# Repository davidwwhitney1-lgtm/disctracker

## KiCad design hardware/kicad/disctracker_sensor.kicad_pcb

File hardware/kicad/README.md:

# DiscTracker sensor board — KiCad 9 project

Open `disctracker_sensor.kicad_pro` in KiCad 9.
- Schematic `disctracker_sensor.kicad_sch`: ERC 0 errors / 0 warnings.
- PCB `disctracker_sensor.kicad_pcb`: **DRC 0 violations, 0 unconnected, schematic parity clean** (all severities).
- Ready-to-order files in `fab/` (see "Ordering").

## Board
| | |
|---|---|
| Size | 56 mm round, flat at x = +26.5 mm for the USB-C plug |
| Stack | 4 layers, 0.8 mm: F.Cu signals + GND pour · In1 **solid GND plane (no signals)** · In2 +3V3 pour (4 short signal segments) · B.Cu signals + GND pour |
| Rules | 0.127 mm tracks (0.25 mm power), 0.12 mm clearance, vias 0.45/0.25 mm — within JLCPCB 4-layer standard |
| Sensor face (top, machine assembled) | U1–U6, C1–C11, R1–R9, JP1 |
| XIAO face (bottom, hand-soldered) | M1 XIAO, BZ1 buzzer, C12, J1/J2 battery pads, TP1–TP4 trim pads, battery outline |
| Not fitted (pair B) | U4, U5, C7–C10, R7, R8 |

Coordinates (origin = U1 = board center, +X toward the USB-C flat, seen from the sensor face):
U2/U3 at (±20.00, 0), U4/U5 at (0, ±20.00), U6 at (0, −25.0), XIAO center (+15, 0) with USB-C at the flat,
battery center (−6.54, 0), holes at r = 25.6 mm (30°/150°/250°), trim pads at r = 22 mm on the diagonals.

## Assembly notes
1. JLCPCB assembles the sensor face (`fab/bom_jlc.csv`, `fab/cpl_jlc.csv`). The LSM6DSV320X has no LCSC number:
   have JLC source it, or consign 3 chips. Check part rotations in JLC's placement preview (pin-1 dots).
2. Bridge **JP1 pads 2–3** (buzzer) with solder.
3. Solder the XIAO flat on the bottom by its castellated edges. Its underside **VBAT and GND pads are plated holes**
   on this board: from the sensor face, feed solder into the two holes next to the XIAO outline to join them.
4. Solder BZ1 and C12 on the bottom; battery leads to J1 (+) / J2 (−); bond the battery inside its silkscreen outline.
5. Weigh and spin-balance the finished pod; add solder to TP1–TP4 to trim.

## Ordering (JLCPCB)
- PCB: upload `fab/disctracker_sensor_gerbers.zip` — 4 layers, 0.8 mm, any color, "specify layer sequence" not needed.
- Assembly: top side, `fab/bom_jlc.csv` + `fab/cpl_jlc.csv`. Passives use JLC basic parts (confirm stock).
- Full parts list incl. hand-soldered parts: `fab/bom_all.csv`. Board-only STEP for the housing CAD: `fab/disctracker_sensor.step`
  (export again from your own KiCad with 3D libraries installed to include the parts).

## Known items
- Two vias sit under **U5** (not fitted on the first build). Move them before fitting pair B; U1–U4 have nothing under them.
- MMC5603NJ footprint (`Package_BGA:WLP-4_0.86x0.86mm_P0.4mm`): confirm ball pitch/pad size against MEMSIC's drawing.
- LGA-14 footprint vs ST TN0018 land pattern: KiCad's standard pattern for this package family.
- XIAO underside SWD/NFC pads are present as unconnected copper (footprint from Seeed's OPL library, CC BY-SA 4.0).

## How it was built (`gen/`)
1. `gen.py` — schematic + symbol library (don't re-run once you edit in KiCad; it also rewrites the .kicad_pro).
2. `xiao_fp.py` — XIAO footprint tweaks (plated VBAT/GND holes, outline on fab layer).
3. `pcb.py <dir> <netlist>` — placement, outline, planes, keepouts, silkscreen, locked GND fan-out under each IMU.
4. `route.py` — Freerouting 2.1 autoroute (In1 kept as a plane), then GND pours.
5. `stitch.py` — GND stitching vias (3 mm grid); `fixups.py` + `padvia.py` — hand fixes for this route; `check_gnd.py` — GND connectivity check.
6. `fab.sh` + `jlc.py` — DRC, Gerbers, drills, pick-and-place, BOMs, STEP, renders.
Autorouting isn't deterministic, so `fixups.py` only applies to the committed route. From here on, edit the PCB in KiCad.

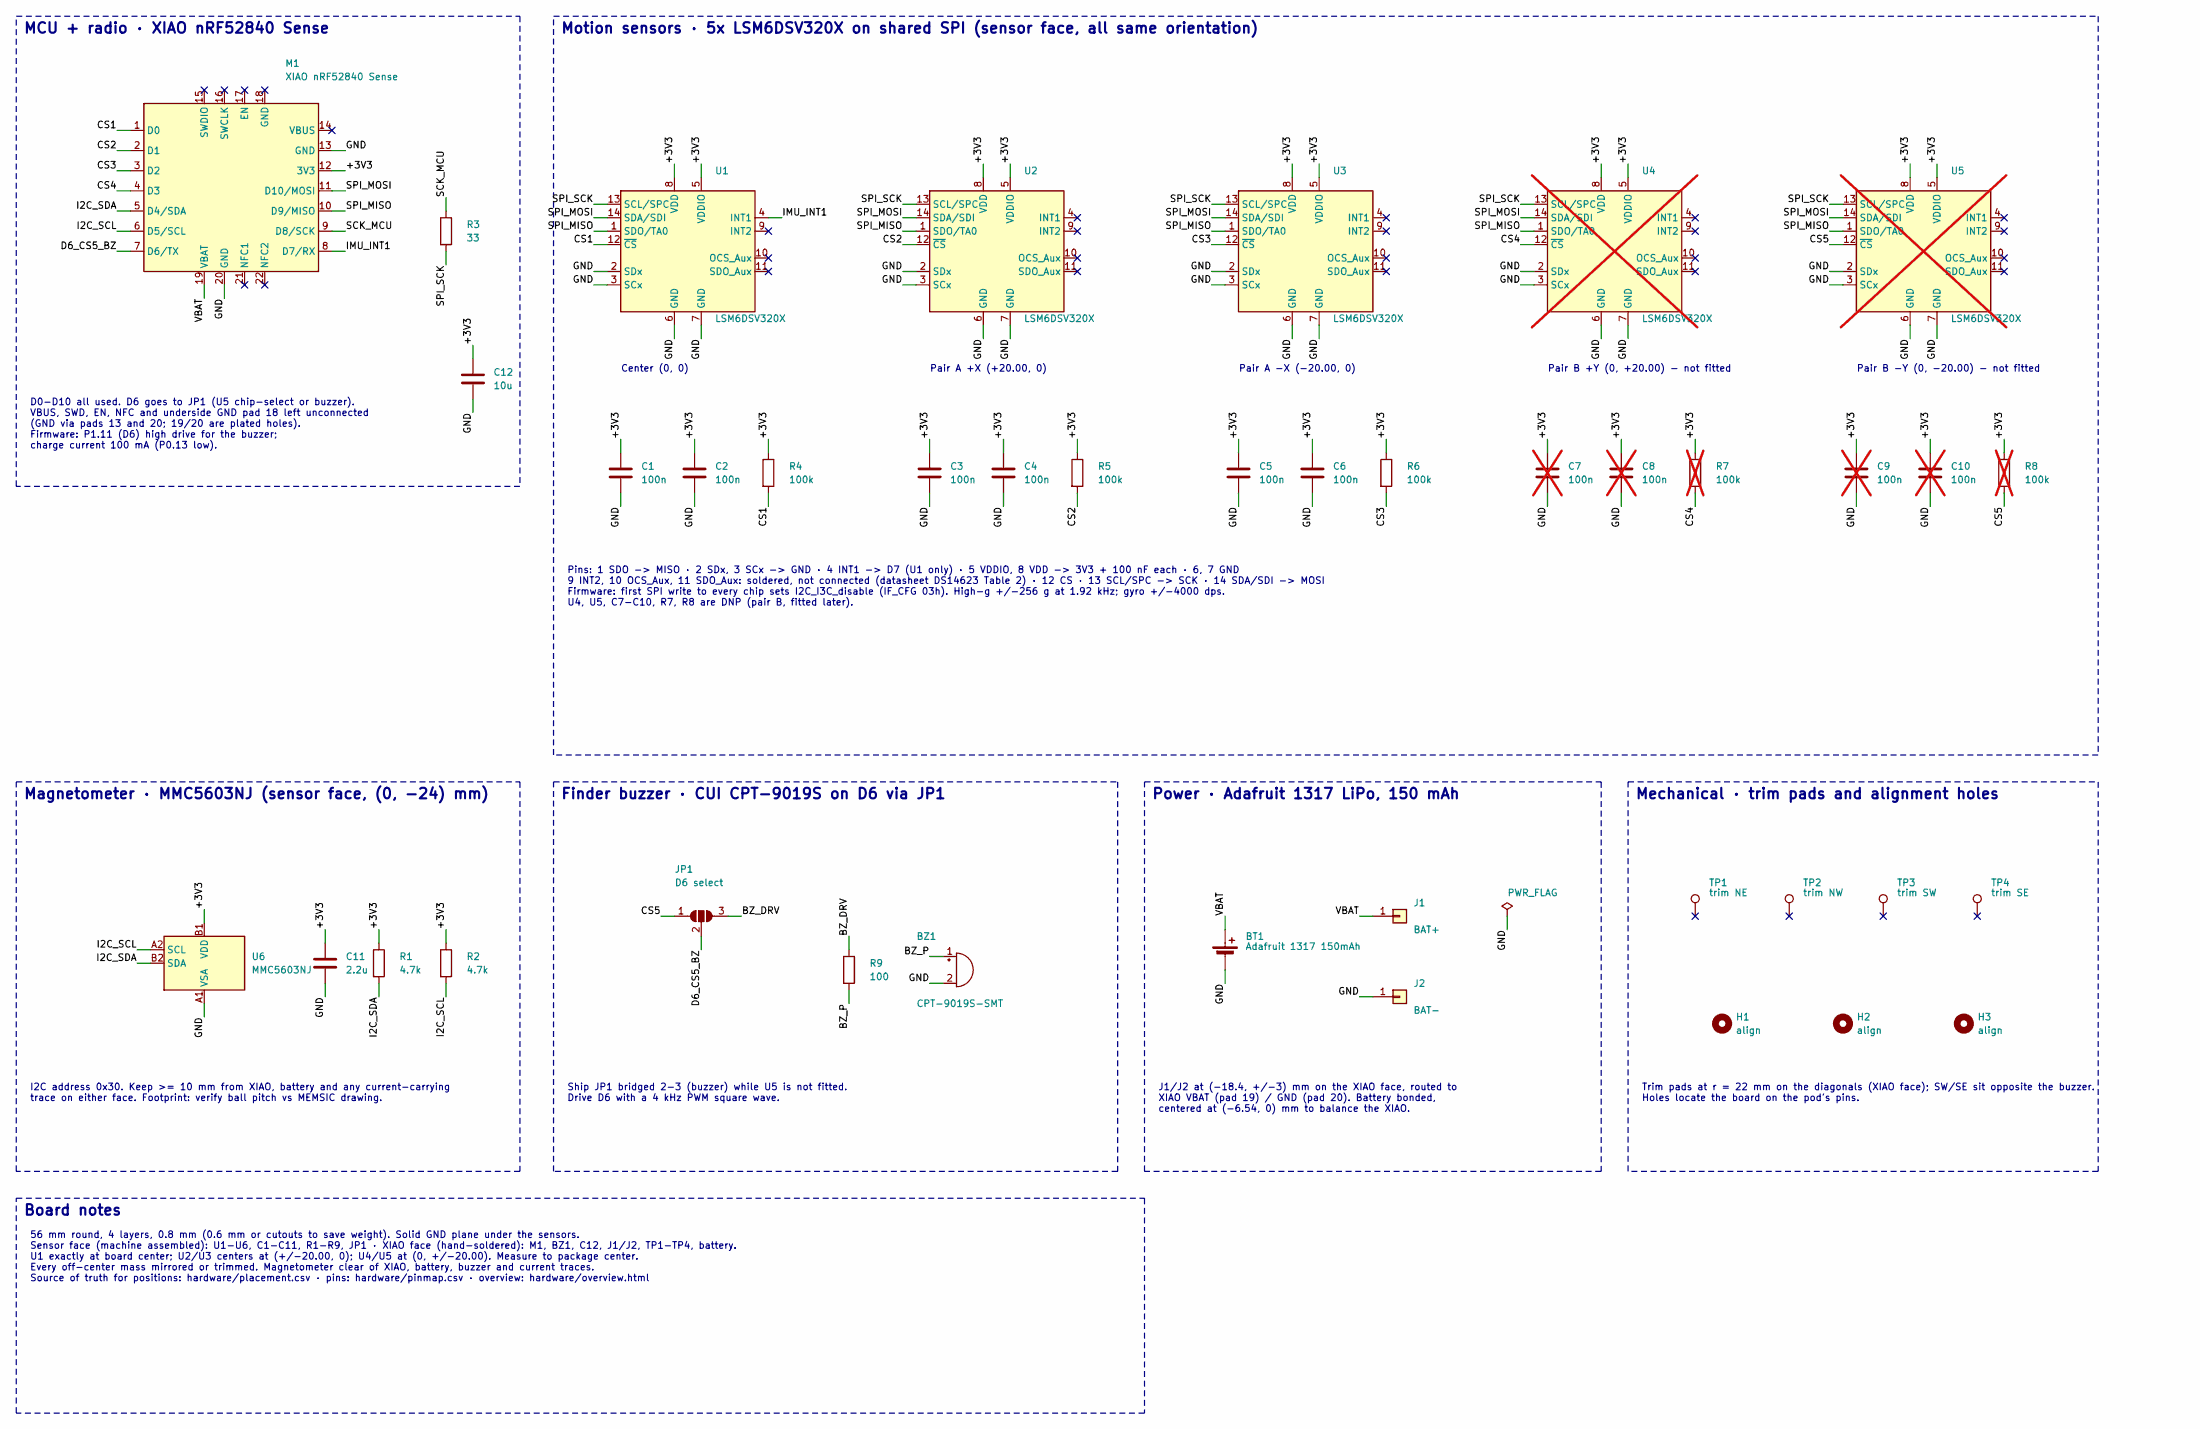
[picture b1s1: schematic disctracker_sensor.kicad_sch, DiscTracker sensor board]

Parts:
BT1: Adafruit 1317 150mAh; MPN Adafruit 1317
BZ1: CPT-9019S-SMT; Buzzer_CUI_CPT-9019S-SMT; MPN CPT-9019S-SMT-TR; LCSC C95163
C1, C2, C3, C4, C5, C6: 100n; C_0402_1005Metric
C7, C8, C9, C10: 100n; C_0402_1005Metric; not fitted
C11: 2.2u; C_0402_1005Metric
C12: 10u; C_0603_1608Metric
H1, H2, H3: align; MountingHole_2.1mm
J1: BAT+; SolderWirePad_1x01_SMD_1.5x3mm
J2: BAT-; SolderWirePad_1x01_SMD_1.5x3mm
JP1: D6 select; SolderJumper-3_P1.3mm_Open_RoundedPad1.0x1.5mm
M1: XIAO nRF52840 Sense; XIAO-nRF52840-SMD; MPN Seeed 102010469
R1, R2: 4.7k; R_0402_1005Metric
R3: 33; R_0402_1005Metric
R4, R5, R6: 100k; R_0402_1005Metric
R7, R8: 100k; R_0402_1005Metric; not fitted
R9: 100; R_0402_1005Metric
TP1: trim NE; TestPoint_Pad_3.0x3.0mm
TP2: trim NW; TestPoint_Pad_3.0x3.0mm
TP3: trim SW; TestPoint_Pad_3.0x3.0mm
TP4: trim SE; TestPoint_Pad_3.0x3.0mm
U1, U2, U3: LSM6DSV320X; LGA-14_3x2.5mm_P0.5mm_LayoutBorder3x4y; MPN LSM6DSV320XTR
U4, U5: LSM6DSV320X; LGA-14_3x2.5mm_P0.5mm_LayoutBorder3x4y; MPN LSM6DSV320XTR; not fitted
U6: MMC5603NJ; WLP-4_0.86x0.86mm_P0.4mm; MPN MMC5603NJ; LCSC C404328

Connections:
/+3V3: C1.1, C2.1, C3.1, C4.1, C5.1, C6.1, C7.1, C8.1, C9.1, C10.1, C11.1, C12.1, M1.12 (3V3), R1.1, R2.1, R4.1, R5.1, R6.1, R7.1, R8.1, U1.5 (VDDIO), U1.8 (VDD), U2.5 (VDDIO), U2.8 (VDD), U3.5 (VDDIO), U3.8 (VDD), U4.5 (VDDIO), U4.8 (VDD), U5.5 (VDDIO), U5.8 (VDD), U6.B1 (VDD)
/BZ_DRV: JP1.3 (B), R9.1
/BZ_P: BZ1.1 (+), R9.2
/CS1: M1.1 (D0), R4.2, U1.12 (~CS)
/CS2: M1.2 (D1), R5.2, U2.12 (~CS)
/CS3: M1.3 (D2), R6.2, U3.12 (~CS)
/CS4: M1.4 (D3), R7.2, U4.12 (~CS)
/CS5: JP1.1 (A), R8.2, U5.12 (~CS)
/D6_CS5_BZ: JP1.2 (C), M1.7 (D6/TX)
/GND: BT1.2 (-), BZ1.2 (-), C1.2, C2.2, C3.2, C4.2, C5.2, C6.2, C7.2, C8.2, C9.2, C10.2, C11.2, C12.2, J2.1, M1.13 (GND), M1.20 (GND), U1.2 (SDx), U1.3 (SCx), U1.6 (GND), U1.7 (GND), U2.2 (SDx), U2.3 (SCx), U2.6 (GND), U2.7 (GND), U3.2 (SDx), U3.3 (SCx), U3.6 (GND), U3.7 (GND), U4.2 (SDx), U4.3 (SCx), U4.6 (GND), U4.7 (GND), U5.2 (SDx), U5.3 (SCx), U5.6 (GND), U5.7 (GND), U6.A1 (VSA)
/I2C_SCL: M1.6 (D5/SCL), R2.2, U6.A2 (SCL)
/I2C_SDA: M1.5 (D4/SDA), R1.2, U6.B2 (SDA)
/IMU_INT1: M1.8 (D7/RX), U1.4 (INT1)
/SCK_MCU: M1.9 (D8/SCK), R3.1
/SPI_MISO: M1.10 (D9/MISO), U1.1 (SDO/TA0), U2.1 (SDO/TA0), U3.1 (SDO/TA0), U4.1 (SDO/TA0), U5.1 (SDO/TA0)
/SPI_MOSI: M1.11 (D10/MOSI), U1.14 (SDA/SDI), U2.14 (SDA/SDI), U3.14 (SDA/SDI), U4.14 (SDA/SDI), U5.14 (SDA/SDI)
/SPI_SCK: R3.2, U1.13 (SCL/SPC), U2.13 (SCL/SPC), U3.13 (SCL/SPC), U4.13 (SCL/SPC), U5.13 (SCL/SPC)
/VBAT: BT1.1 (+), J1.1, M1.19 (VBAT)

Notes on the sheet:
MCU + radio · XIAO nRF52840 Sense
D0-D10 all used. D6 goes to JP1 (U5 chip-select or buzzer). VBUS, SWD, EN, NFC and underside GND pad 18 left unconnected (GND via pads 13 and 20; 19/20 are plated holes). Firmware: P1.11 (D6) high drive for the buzzer; charge current 100 mA (P0.13 low).
Motion sensors · 5x LSM6DSV320X on shared SPI (sensor face, all same orientation)
Center (0, 0)
Pair A +X (+20.00, 0)
Pair A -X (-20.00, 0)
Pair B +Y (0, +20.00) - not fitted
Pair B -Y (0, -20.00) - not fitted
Pins: 1 SDO -> MISO · 2 SDx, 3 SCx -> GND · 4 INT1 -> D7 (U1 only) · 5 VDDIO, 8 VDD -> 3V3 + 100 nF each · 6, 7 GND 9 INT2, 10 OCS_Aux, 11 SDO_Aux: soldered, not connected (datasheet DS14623 Table 2) · 12 CS · 13 SCL/SPC -> SCK · 14 SDA/SDI -> MOSI Firmware: first SPI write to every chip sets I2C_I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
Magnetometer · MMC5603NJ (sensor face, (0, -24) mm)
I2C address 0x30. Keep >= 10 mm from XIAO, battery and any current-carrying trace on either face. Footprint: verify ball pitch vs MEMSIC drawing.
Finder buzzer · CUI CPT-9019S on D6 via JP1
Ship JP1 bridged 2-3 (buzzer) while U5 is not fitted. Drive D6 with a 4 kHz PWM square wave.
Power · Adafruit 1317 LiPo, 150 mAh
J1/J2 at (-18.4, +/-3) mm on the XIAO face, routed to XIAO VBAT (pad 19) / GND (pad 20). Battery bonded, centered at (-6.54, 0) mm to balance the XIAO.
Mechanical · trim pads and alignment holes
Trim pads at r = 22 mm on the diagonals (XIAO face); SW/SE sit opposite the buzzer. Holes locate the board on the pod's pins.
Board notes
56 mm round, 4 layers, 0.8 mm (0.6 mm or cutouts to save weight). Solid GND plane under the sensors. Sensor face (machine assembled): U1-U6, C1-C11, R1-R9, JP1 · XIAO face (hand-soldered): M1, BZ1, C12, J1/J2, TP1-TP4, battery. U1 exactly at board center; U2/U3 centers at (+/-20.00, 0); U4/U5 at (0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

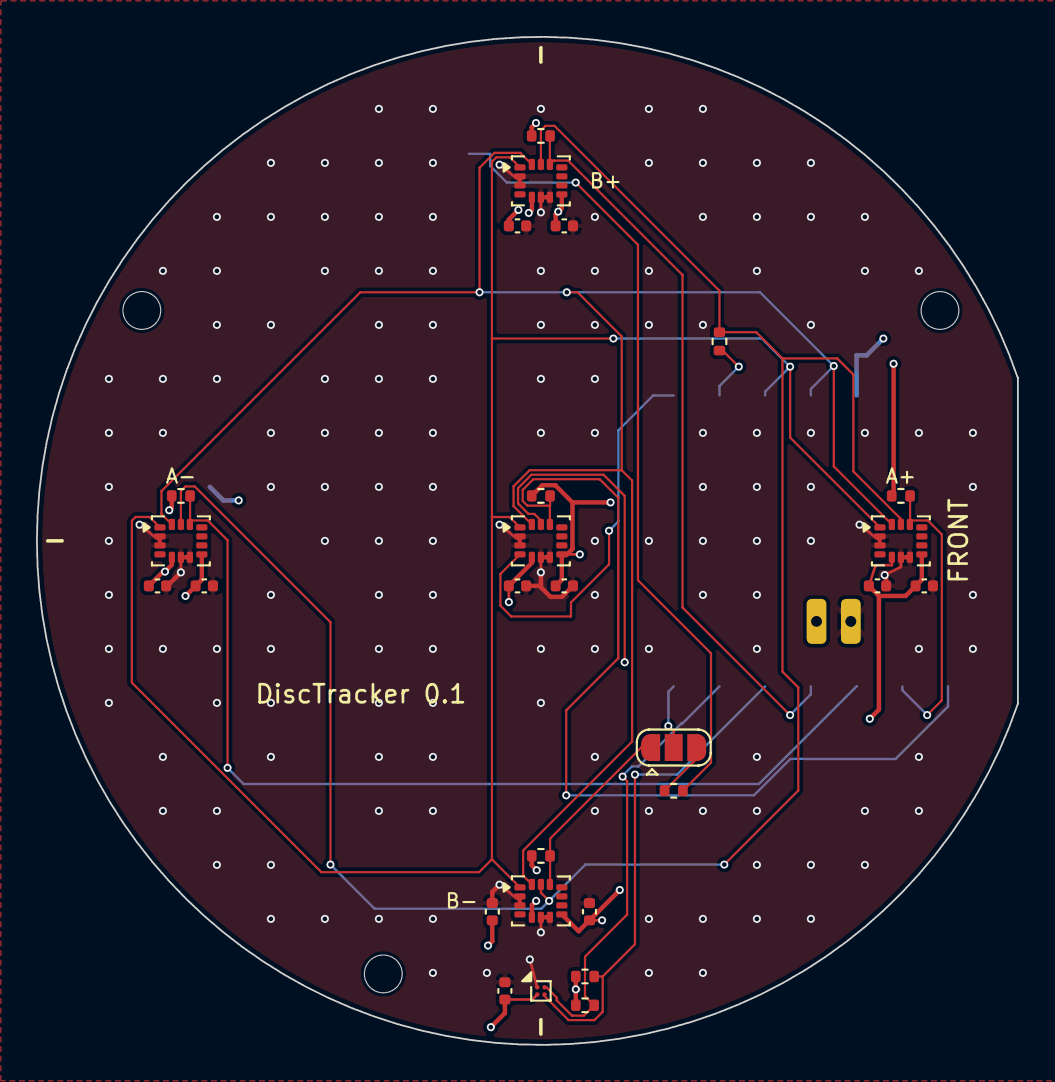
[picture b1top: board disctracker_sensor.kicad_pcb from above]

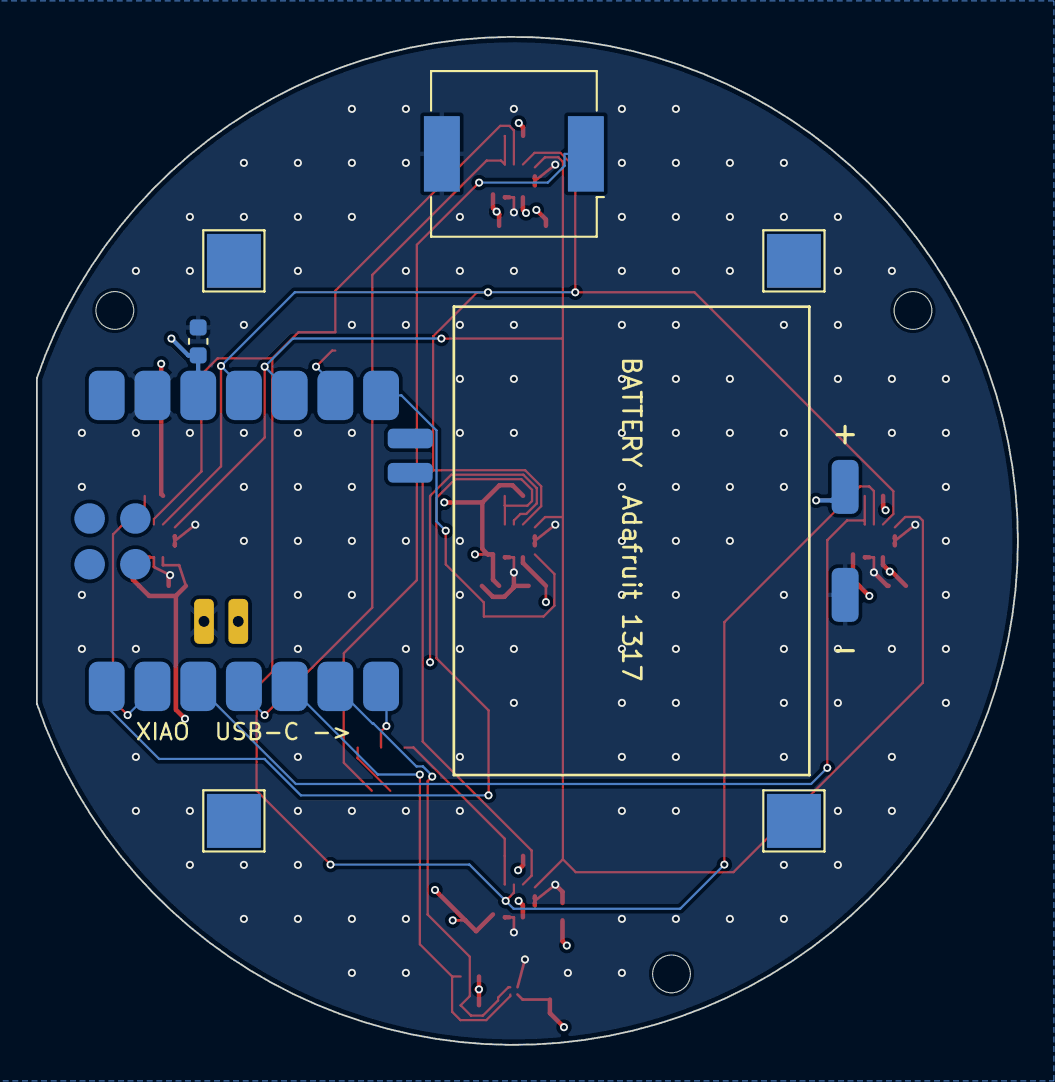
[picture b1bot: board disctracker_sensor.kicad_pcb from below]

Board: 4 copper layers, 54.5 x 56.0 mm, 39 parts (9 on the bottom side), 18 nets.

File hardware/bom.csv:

Ref,Part,Value,Package,Qty,Populate,Face,Notes
U1,ST LSM6DSV320X,,LGA-14 2.5x3.0x0.83,1,Yes,Sensor,Center IMU
U2,ST LSM6DSV320X,,LGA-14 2.5x3.0x0.83,1,Yes,Sensor,Spin pair A (+20.00; 0)
U3,ST LSM6DSV320X,,LGA-14 2.5x3.0x0.83,1,Yes,Sensor,Spin pair A (-20.00; 0)
U4,ST LSM6DSV320X,,LGA-14 2.5x3.0x0.83,1,DNP,Sensor,Spin pair B (0; +20.00)
U5,ST LSM6DSV320X,,LGA-14 2.5x3.0x0.83,1,DNP,Sensor,Spin pair B (0; -20.00)
U6,MEMSIC MMC5603NJ,,WLCSP 0.8x0.8,1,Yes,Sensor,Magnetometer at (0; -24); JLCPCB C404328; I2C 0x30
C1-C10,Capacitor,100 nF,0402,10,6 of 10,Sensor,VDD (pin 8) + VDDIO (pin 5) per IMU; C7-C10 DNP with U4/U5
C11,Capacitor,2.2 uF,0402,1,Yes,Sensor,Magnetometer VDD (datasheet minimum 2.2 uF)
C12,Capacitor,10 uF,0603,1,Yes,XIAO,Bulk at XIAO 3V3
R1 R2,Resistor,4.7 k,0402,2,Yes,Sensor,I2C pull-ups (magnetometer)
R3,Resistor,33 R,0402,1,Yes,Sensor,Series on SPI clock
R4-R8,Resistor,100 k,0402,5,Yes,Sensor,CS pull-ups to 3V3 (firmware disables chips' internal pull-up with I2C_I3C_disable)
M1,Seeed XIAO nRF52840 Sense,,castellated SMD,1,Yes,XIAO,2.027 g / 4.0 mm (measured); center (+15; 0) so USB-C reaches the pod edge; hand-soldered
BZ1,CUI CPT-9019S-SMT-TR,,9x9x1.9 SMD,1,Yes,XIAO,Piezo 3 V / 5 mA / 65 dB @10 cm / 4 kHz; JLCPCB C95163; at (0; +21.5)
JP1,3-pad solder jumper,,SMD,1,Yes,XIAO,D6 -> A: U5 CS / B: BZ1; ship bridged to B
R9,Resistor,100 R,0402,1,Yes,Sensor,Series to buzzer (limits peak current into piezo)
H1-H3,Mounting hole,2.1 mm,NPTH,3,-,Both,Alignment pins; r = 25.6 mm at 30/150/250 deg
BT1,Adafruit 1317 LiPo 3.7 V (protected),150 mAh,19.75x26.02x3.8 mm,1,Yes,XIAO,4.65 g; center (-6.54; 0); bonded down; leads cut short to J1/J2; charge at 100 mA
J1 J2,Battery pads,,pads,2,Yes,XIAO,At (-18.4; +/-3); routed to XIAO BAT pads
TP1-TP4,Balance trim pads,3x3 mm,copper pad,4,Yes,XIAO,+X/-X/+Y/-Y; -Y opposite the buzzer; add solder to trim

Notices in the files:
parts and their libraries:
Seeed XIAO nRF52840, SMD. Pads 19-20 made plated through-holes (DiscTracker). Source: Seeed OPL KiCad library, CC BY-SA 4.0
